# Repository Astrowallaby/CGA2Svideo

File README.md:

# CGA2Svideo
Circuits for converting digital RGBI (CGA) to S-video and other formats

This repo contains a collection of video conversion circuits intended
to convert old-fashioned digital RGBI monitor output as used by the
IBM PC Color Graphics Adapter (CGA) and several other 80's vintage small
computers to more modern and/or more available monitors. (RGBI is a thoroughly obsolete format; there have been very few monitors built since the early 1990's that are able to natively accept it.)

The titular circuit for this repository is a converter that uses an [Analog Devices AD724JR](https://www.analog.com/media/en/technical-documentation/data-sheets/AD724.pdf) NTSC/PAL encoder along with a GAL16v8 to turn RGBI video into both composite and separated Luma/Chroma (Svideo) output that can be fed into television sets and monitors that have the appropriate input jacks. The Luma/Chroma conversion specifically may be of interest to owners of monitors like the very common Commodore 1701/1702, which were designed to accept this type of input from Commodore 64 computers.

SVideo has lower color resolution than RGB, so the output from this circuit will be inferior to that of a true RGB monitor. But it still provides much clearer output, expecially at 80 columns, than the native composite video jack built into older PC compatible computers. This circuit might particularly be appealing to users of the Tandy 1000 series of computers, as the output is set up to better match the colors you get on an RGBI monitor (verses the odd palette that's normal for CGA composite) and the clarity is more than adequate for 320x200x16 color games.

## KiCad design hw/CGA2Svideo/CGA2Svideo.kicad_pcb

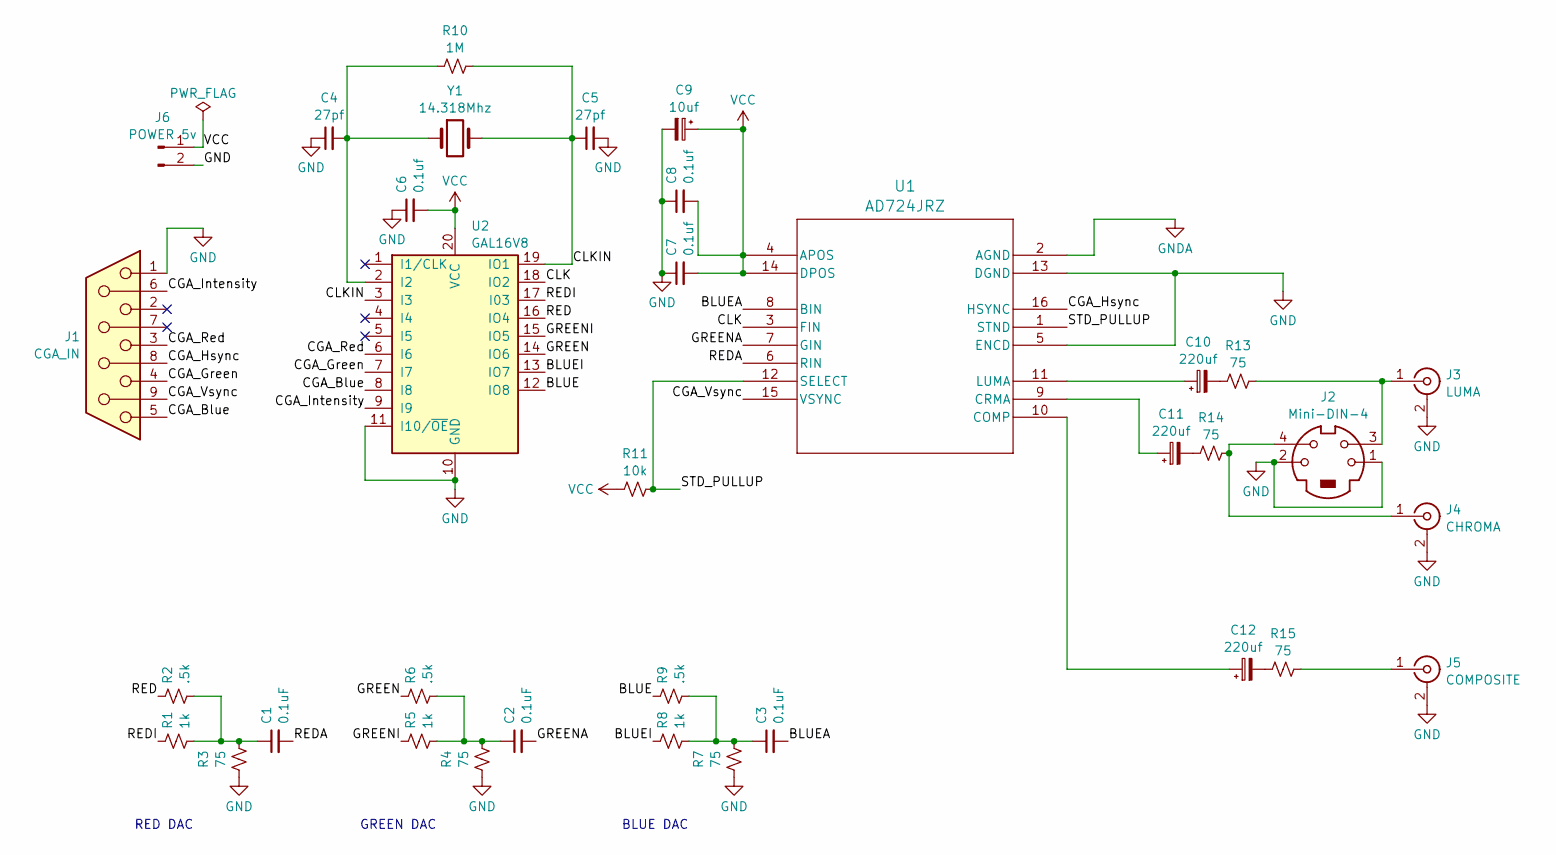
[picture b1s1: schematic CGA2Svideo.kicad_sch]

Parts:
C1, C2, C3: 0.1uF; C_Disc_D7.5mm_W2.5mm_P5.00mm
C4, C5: 27pf; C_Disc_D7.5mm_W2.5mm_P5.00mm
C6, C7, C8: 0.1uf; C_Disc_D7.5mm_W2.5mm_P5.00mm
C9: 10uf; CP_Radial_D5.0mm_P2.50mm
C10, C11, C12: 220uf; CP_Radial_D5.0mm_P2.50mm
J1: CGA_IN; DSUB-9_Female_Horizontal_P2.77x2.84mm_EdgePinOffset4.94mm_H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
J2: Mini-DIN-4; PinHeader_1x04_P2.54mm_Vertical
J3: LUMA; PinHeader_1x02_P2.54mm_Vertical
J4: CHROMA; PinHeader_1x02_P2.54mm_Vertical
J5: COMPOSITE; PinHeader_1x02_P2.54mm_Vertical
J6: POWER 5v; PinHeader_1x02_P2.54mm_Vertical
R1, R5, R8: 1k; R_Axial_DIN0204_L3.6mm_D1.6mm_P7.62mm_Horizontal
R2, R6, R9: .5k; R_Axial_DIN0204_L3.6mm_D1.6mm_P7.62mm_Horizontal
R3, R4, R7, R13, R14, R15: 75; R_Axial_DIN0204_L3.6mm_D1.6mm_P7.62mm_Horizontal
R10: 1M; R_Axial_DIN0204_L3.6mm_D1.6mm_P7.62mm_Horizontal
R11: 10k; R_Axial_DIN0204_L3.6mm_D1.6mm_P7.62mm_Horizontal
U1: AD724JRZ; SO-16_5.3x10.2mm_P1.27mm
U2: GAL16V8; DIP-20_W7.62mm_Socket_LongPads
Y1: 14.318Mhz; Resonator-2Pin_W10.0mm_H5.0mm

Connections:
/BLUE: R9.1, U2.12 (IO8)
/BLUEA: C3.2, U1.8 (BIN)
/BLUEI: R8.1, U2.13 (IO7)
/CGA_Blue: J1.5, U2.8 (I8)
/CGA_Green: J1.4, U2.7 (I7)
/CGA_Hsync: J1.8, U1.16 (HSYNC)
/CGA_Intensity: J1.6, U2.9 (I9)
/CGA_Red: J1.3, U2.6 (I6)
/CGA_Vsync: J1.9, U1.15 (VSYNC)
/CLK: U1.3 (FIN), U2.18 (IO2)
/CLKIN: C5.1, R10.2, U2.3 (I3), U2.19 (IO1), Y1.2
/GREEN: R6.1, U2.14 (IO6)
/GREENA: C2.2, U1.7 (GIN)
/GREENI: R5.1, U2.15 (IO5)
/RED: R2.1, U2.16 (IO4)
/REDA: C1.2, U1.6 (RIN)
/REDI: R1.1, U2.17 (I03)
/STD_PULLUP: R11.2, U1.1 (STND), U1.12 (SELECT)
GND: C4.1, C5.2, C6.1, C7.1, C8.1, C9.2, J1.1, J2.1, J2.2, J3.2 (Ext), J4.2 (Ext), J5.2 (Ext), J6.2, R3.2, R4.2, R7.2, U1.5 (ENCD), U1.13 (DGND), U2.10 (GND), U2.11 (I10/~OE)
GNDA: U1.2 (AGND)
unnamed: C1.1, R1.2, R2.2, R3.1
unnamed: C2.1, R4.1, R5.2, R6.2
unnamed: C3.1, R7.1, R8.2, R9.2
unnamed: C10.2, R13.1
unnamed: C11.2, R14.1
unnamed: C12.2, R15.1
unnamed: J2.3, J3.1 (In), R13.2
unnamed: J2.4, J4.1 (In), R14.2
unnamed: J5.1 (In), R15.2
unnamed: C12.1, U1.10 (COMP)
unnamed: C11.1, U1.9 (CRMA)
unnamed: C10.1, U1.11 (LUMA)
unnamed: C4.2, R10.1, U2.2 (I2), Y1.1
VCC: C6.2, C7.2, C8.2, C9.1, J6.1, R11.1, U1.4 (APOS), U1.14 (DPOS), U2.20 (VCC)

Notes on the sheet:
RED DAC
GREEN DAC
BLUE DAC

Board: 2 copper layers, 35 parts (0 on the bottom side), 33 nets, no tracks yet.

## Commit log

2025-02-22 Inital checkin of svideo GAL
2025-02-23 initial kicad schematic
